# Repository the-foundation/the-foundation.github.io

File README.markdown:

Spacecraft
==========

This is [Spacecraft](http://spacecraft.org.nz)'s site.

Setup
-----

To check your system has the necessary dependencies, just run:

    script/setup

You can safely run this script as many times as you like.

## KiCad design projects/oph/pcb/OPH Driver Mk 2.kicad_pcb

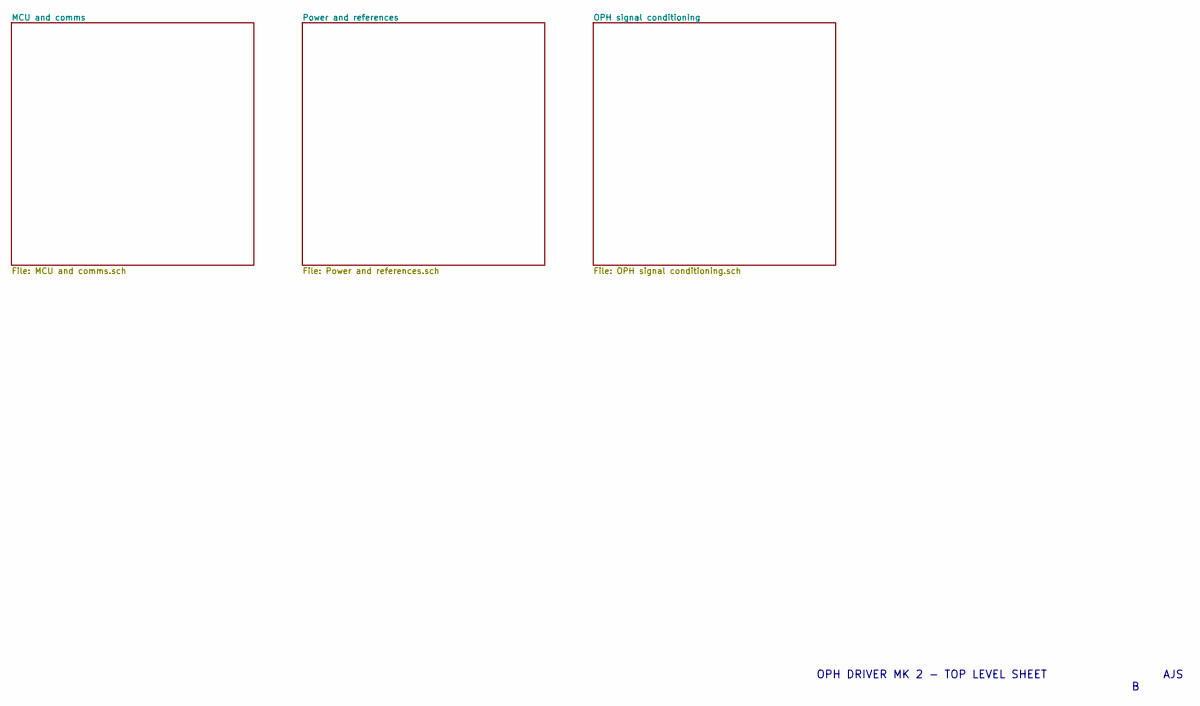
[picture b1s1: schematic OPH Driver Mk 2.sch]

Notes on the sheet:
OPH DRIVER MK 2 - TOP LEVEL SHEET
AJS

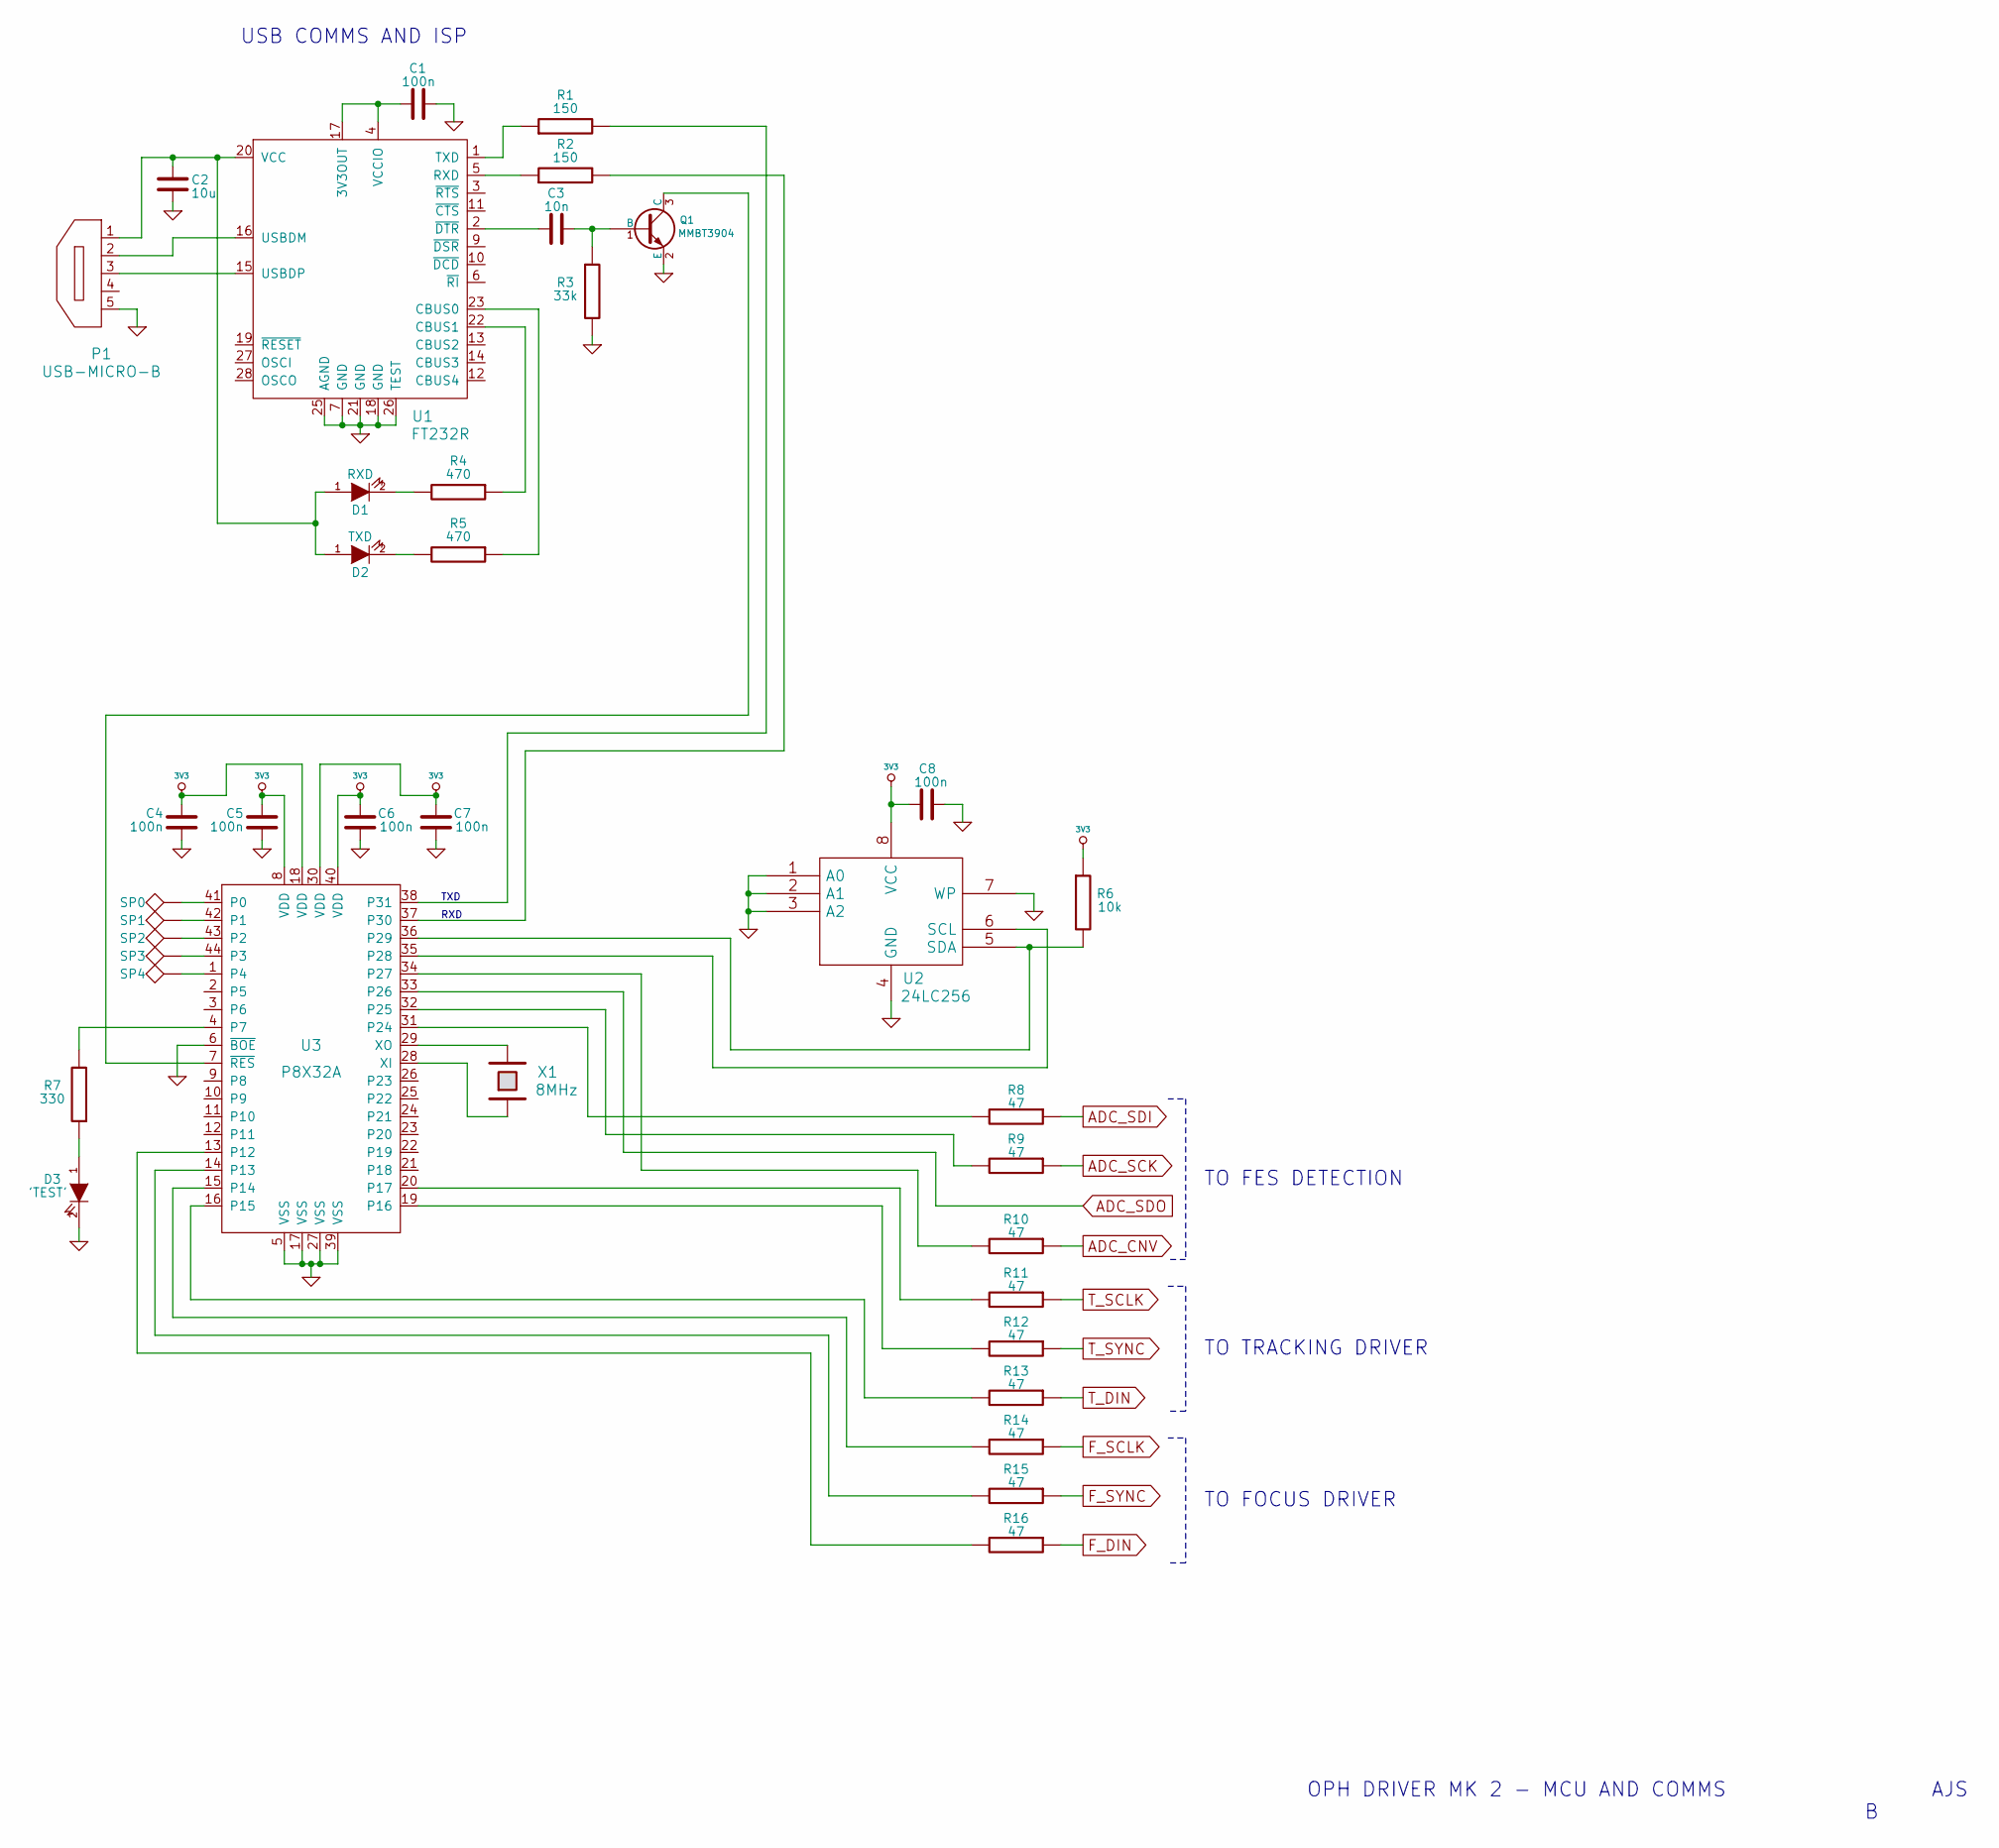
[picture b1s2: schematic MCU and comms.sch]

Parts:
C1, C4, C5, C6, C7, C8: 100n
C2: 10u
C3: 10n
D1: RXD
D2: TXD
D3: 'TEST'
P1: USB-MICRO-B
P2: SP0
P3: SP1
P4: SP2
P5: SP3
P6: SP4
Q1: MMBT3904; SOT-23
R1, R2: 150
R3: 33k
R4, R5: 470
R6: 10k
R7: 330
R8, R9, R10, R11, R12, R13, R14, R15, R16: 47
U1: FT232R
U2: 24LC256
U3: P8X32A
X1: 8MHz

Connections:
3V3: C4.1, C5.1, C6.1, C7.1, C8.2, R6.1, U2.8 (VCC), U3.8 (VDD), U3.18 (VDD), U3.30 (VDD), U3.40 (VDD); also elsewhere on the board
ADC_CNV: R10.1; also elsewhere on the board
ADC_SCK: R9.1; also elsewhere on the board
ADC_SDI: R8.1; also elsewhere on the board
ADC_SDO: U3.33 (P26); also elsewhere on the board
F_DIN: R16.1; also elsewhere on the board
F_SCLK: R14.1; also elsewhere on the board
F_SYNC: R15.1; also elsewhere on the board
GND: C1.2, C2.2, C4.2, C5.2, C6.2, C7.2, C8.1, D3.2 (K), P1.5, Q1.2 (E), R3.2, U1.7 (GND), U1.18 (GND), U1.21 (GND), U1.25 (AGND), U1.26 (TEST), U2.1 (A0), U2.2 (A1), U2.3 (A2), U2.4 (GND), U2.7 (WP), U3.5 (VSS), U3.6 (~BOE), U3.17 (VSS), U3.27 (VSS), U3.39 (VSS); also elsewhere on the board
unnamed: C1.1, U1.4 (VCCIO), U1.17 (3V3OUT)
unnamed: C2.1, D1.1 (A), D2.1 (A), P1.1, U1.20 (VCC)
unnamed: C3.1, U1.2 (~DTR)
unnamed: C3.2, Q1.1 (B), R3.1
unnamed: D1.2 (K), R4.2
unnamed: D2.2 (K), R5.2
unnamed: D3.1 (A), R7.1
unnamed: P1.2, U1.16 (USBDM)
unnamed: P1.3, U1.15 (USBDP)
unnamed: P2.1, U3.41 (P0)
unnamed: P3.1, U3.42 (P1)
unnamed: P4.1, U3.43 (P2)
unnamed: P5.1, U3.44 (P3)
unnamed: P6.1, U3.1 (P4)
unnamed: Q1.3 (C), U3.7 (~RES)
unnamed: R1.1, U1.1 (TXD)
unnamed: R1.2, U3.38 (P31)
unnamed: R2.1, U1.5 (RXD)
unnamed: R2.2, U3.37 (P30)
unnamed: R4.1, U1.22 (CBUS1)
unnamed: R5.1, U1.23 (CBUS0)
unnamed: R6.2, U2.5 (SDA), U3.36 (P29)
unnamed: R7.2, U3.4 (P7)
unnamed: R8.2, U3.31 (P24)
unnamed: R9.2, U3.32 (P25)
unnamed: R10.2, U3.34 (P27)
unnamed: R11.2, U3.20 (P17)
unnamed: R12.2, U3.19 (P16)
unnamed: R13.2, U3.16 (P15)
unnamed: R14.2, U3.15 (P14)
unnamed: R15.2, U3.14 (P13)
unnamed: R16.2, U3.13 (P12)
unnamed: U2.6 (SCL), U3.35 (P28)
unnamed: U3.28 (XI), X1.1
unnamed: U3.29 (XO), X1.2
T_DIN: R13.1; also elsewhere on the board
T_SCLK: R11.1; also elsewhere on the board
T_SYNC: R12.1; also elsewhere on the board

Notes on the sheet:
TXD
RXD
TO TRACKING DRIVER
USB COMMS AND ISP
OPH DRIVER MK 2 - MCU AND COMMS
TO FES DETECTION
TO FOCUS DRIVER
AJS

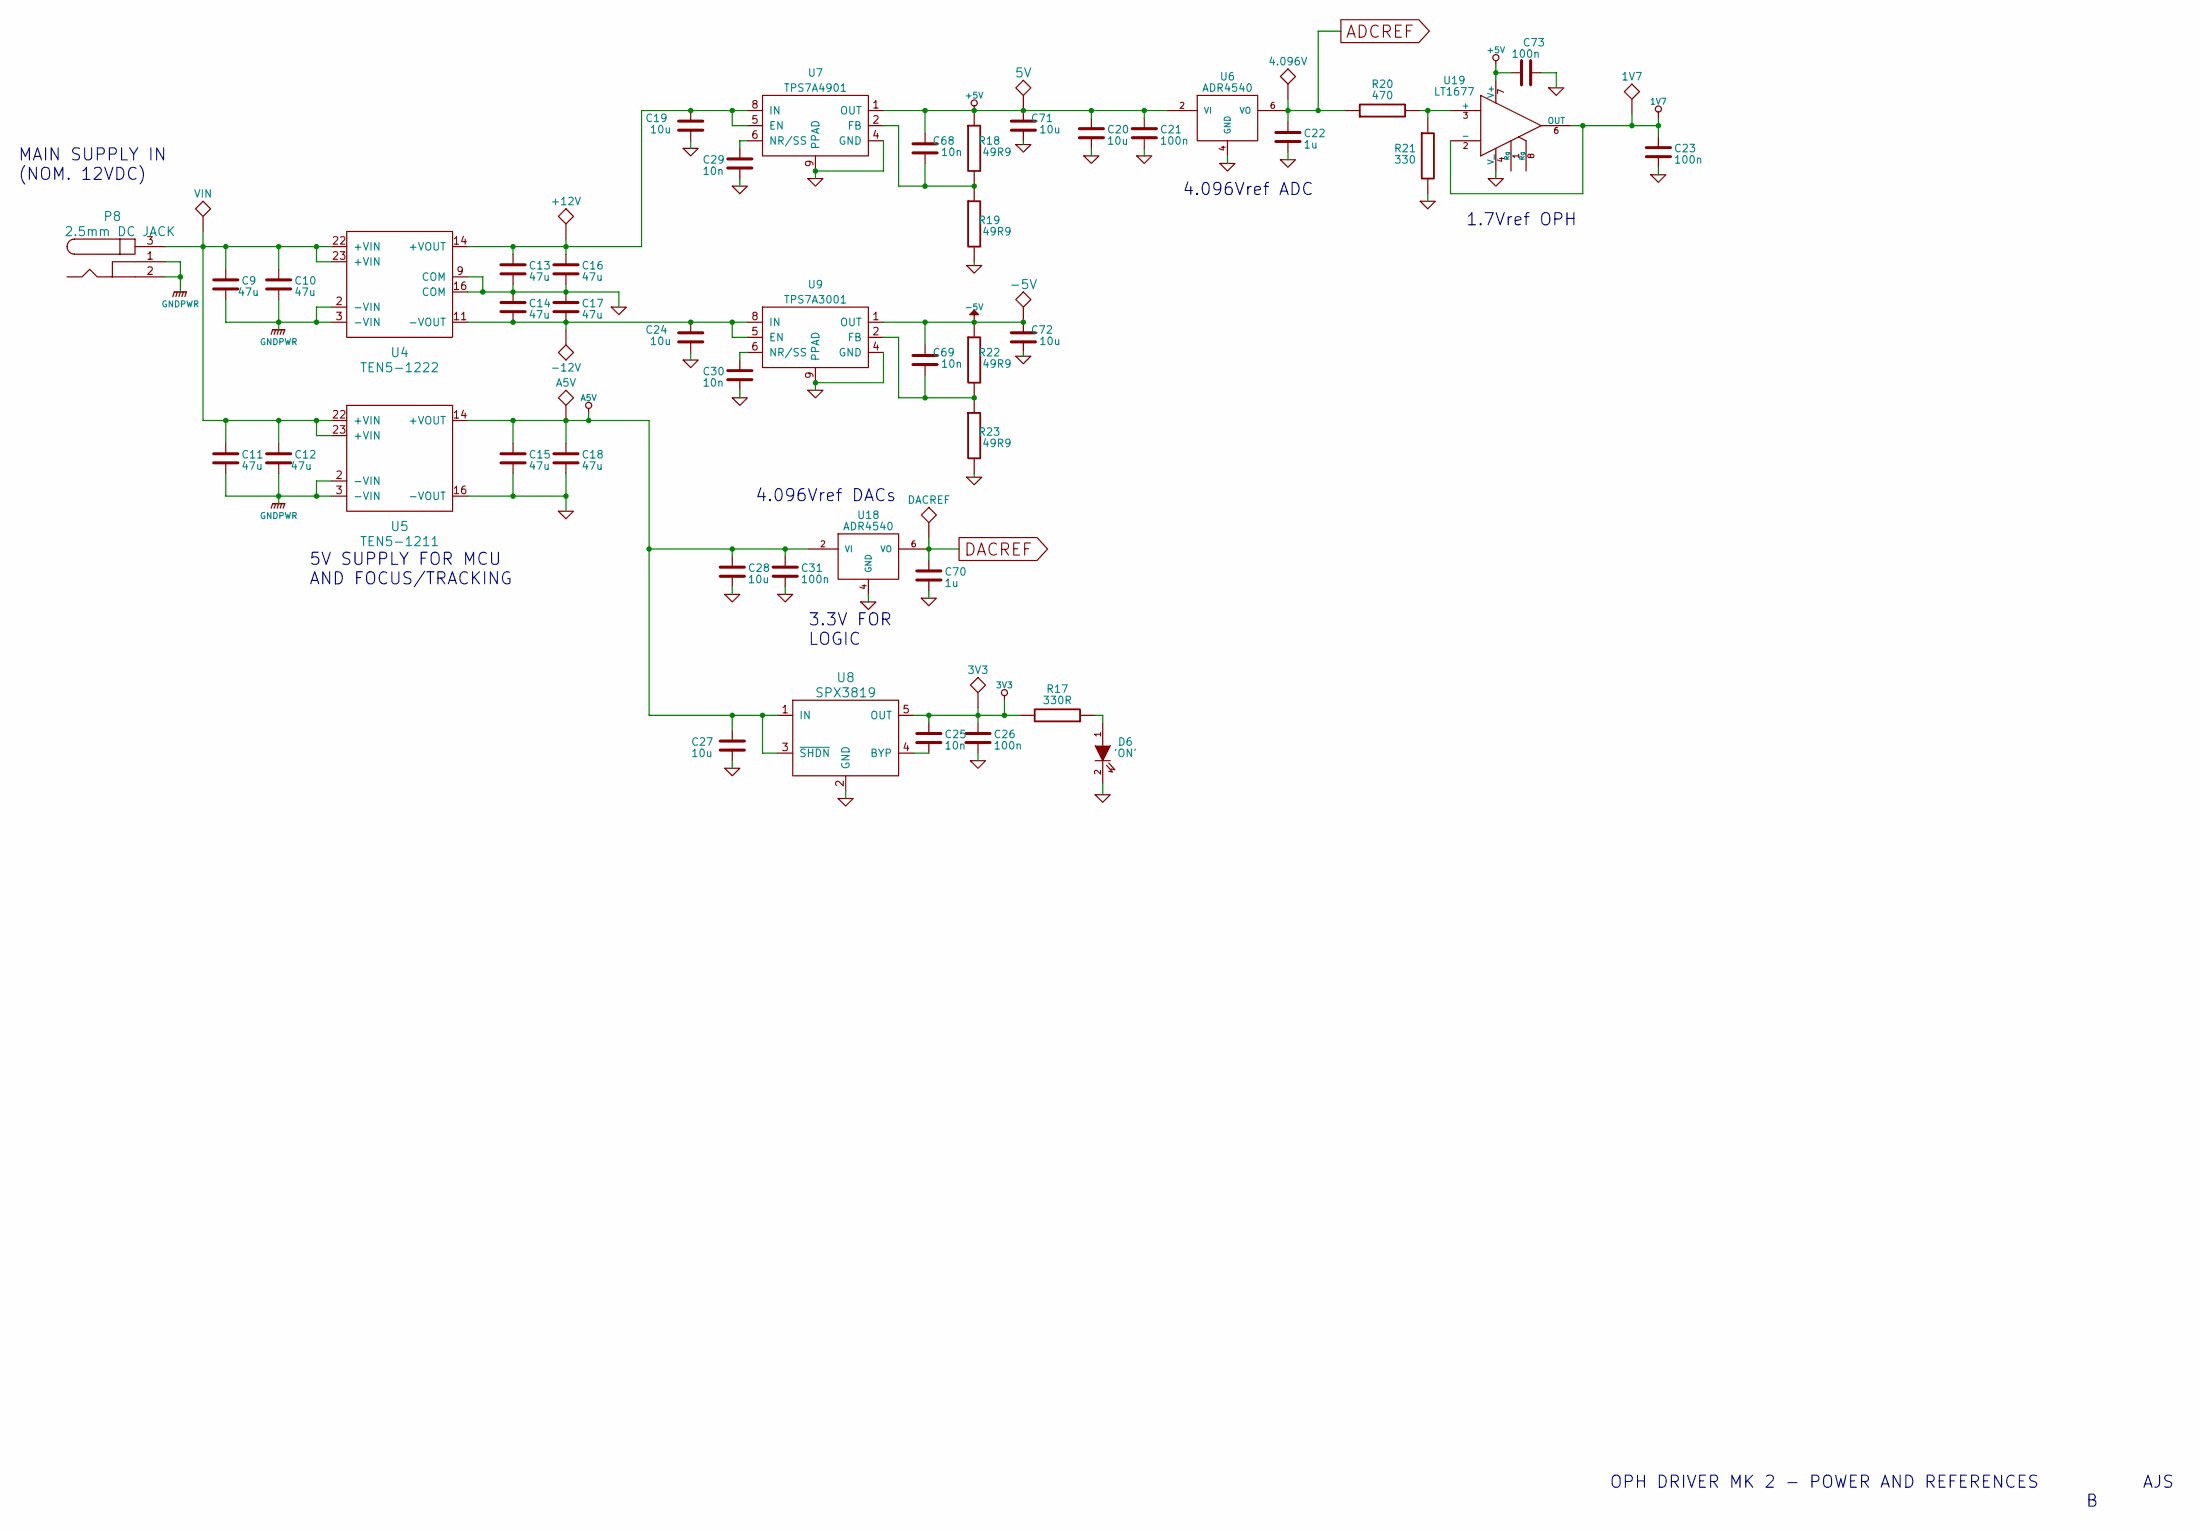
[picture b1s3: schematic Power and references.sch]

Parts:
C9, C10, C11, C12, C13, C14, C15, C16, C17, C18: 47u
C19, C20, C24, C27, C28, C71, C72: 10u
C21, C23, C26, C31, C73: 100n
C22, C70: 1u
C25, C29, C30, C68, C69: 10n
D6: 'ON'
P7: VIN
P8: 2.5mm DC JACK
P9: +12V
P10: 5V
P11: 4.096V
P12: 1V7
P13: A5V
P14: 3V3
P15: -12V
P51: DACREF
P52: -5V
R17: 330R
R18, R19, R22, R23: 49R9
R20: 470
R21: 330
U4: TEN5-1222
U5: TEN5-1211
U6, U18: ADR4540
U7: TPS7A4901
U8: SPX3819
U9: TPS7A3001
U19: LT1677

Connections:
1V7: C23.1, P12.1, U19.2 (-), U19.6 (OUT); also elsewhere on the board
3V3: C25.1, C26.1, P14.1, R17.2, U8.5 (OUT); also elsewhere on the board
-5V: C69.2, C72.2, P52.1, R22.1, U9.1 (OUT); also elsewhere on the board
A5V: C15.1, C18.1, C27.1, C28.1, C31.1, P13.1, U5.14 (+VOUT), U8.1 (IN), U8.3 (~SHDN), U18.2 (VI); also elsewhere on the board
ADCREF: C22.1, P11.1, R20.1, U6.6 (VO); also elsewhere on the board
DACREF: C70.1, P51.1, U18.6 (VO); also elsewhere on the board
GND: C13.2, C14.1, C15.2, C16.2, C17.1, C18.2, C19.1, C20.2, C21.2, C22.2, C23.2, C24.1, C26.2, C27.2, C28.2, C29.2, C30.2, C31.2, C70.2, C71.1, C72.1, C73.1, D6.2 (K), R19.2, R21.2, R23.2, U4.9 (COM), U4.16 (COM), U5.16 (-VOUT), U6.4 (GND), U7.4 (GND), U7.9 (PPAD), U8.2 (GND), U9.4 (GND), U9.9 (PPAD), U18.4 (GND), U19.4 (V_); also elsewhere on the board
GNDPWR: C9.2, C10.2, C11.2, C12.2, P8.1, P8.2, U4.2 (-VIN), U4.3 (-VIN), U5.2 (-VIN), U5.3 (-VIN)
unnamed: C9.1, C10.1, C11.1, C12.1, P7.1, P8.3, U4.22 (+VIN), U4.23 (+VIN), U5.22 (+VIN), U5.23 (+VIN)
unnamed: C13.1, C16.1, C19.2, P9.1, U4.14 (+VOUT), U7.5 (EN), U7.8 (IN)
unnamed: C14.2, C17.2, C24.2, P15.1, U4.11 (-VOUT), U9.5 (EN), U9.8 (IN)
unnamed: C25.2, U8.4 (BYP)
unnamed: C29.1, U7.6 (NR/SS)
unnamed: C30.1, U9.6 (NR/SS)
unnamed: C68.1, R18.2, R19.1, U7.2 (FB)
unnamed: C69.1, R22.2, R23.1, U9.2 (FB)
unnamed: D6.1 (A), R17.1
unnamed: R20.2, R21.1, U19.3 (+)

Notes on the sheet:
5V SUPPLY FOR MCU AND FOCUS/TRACKING
4.096Vref ADC
MAIN SUPPLY IN (NOM. 12VDC)
1.7Vref OPH
3.3V FOR LOGIC
OPH DRIVER MK 2 - POWER AND REFERENCES
AJS
4.096Vref DACs

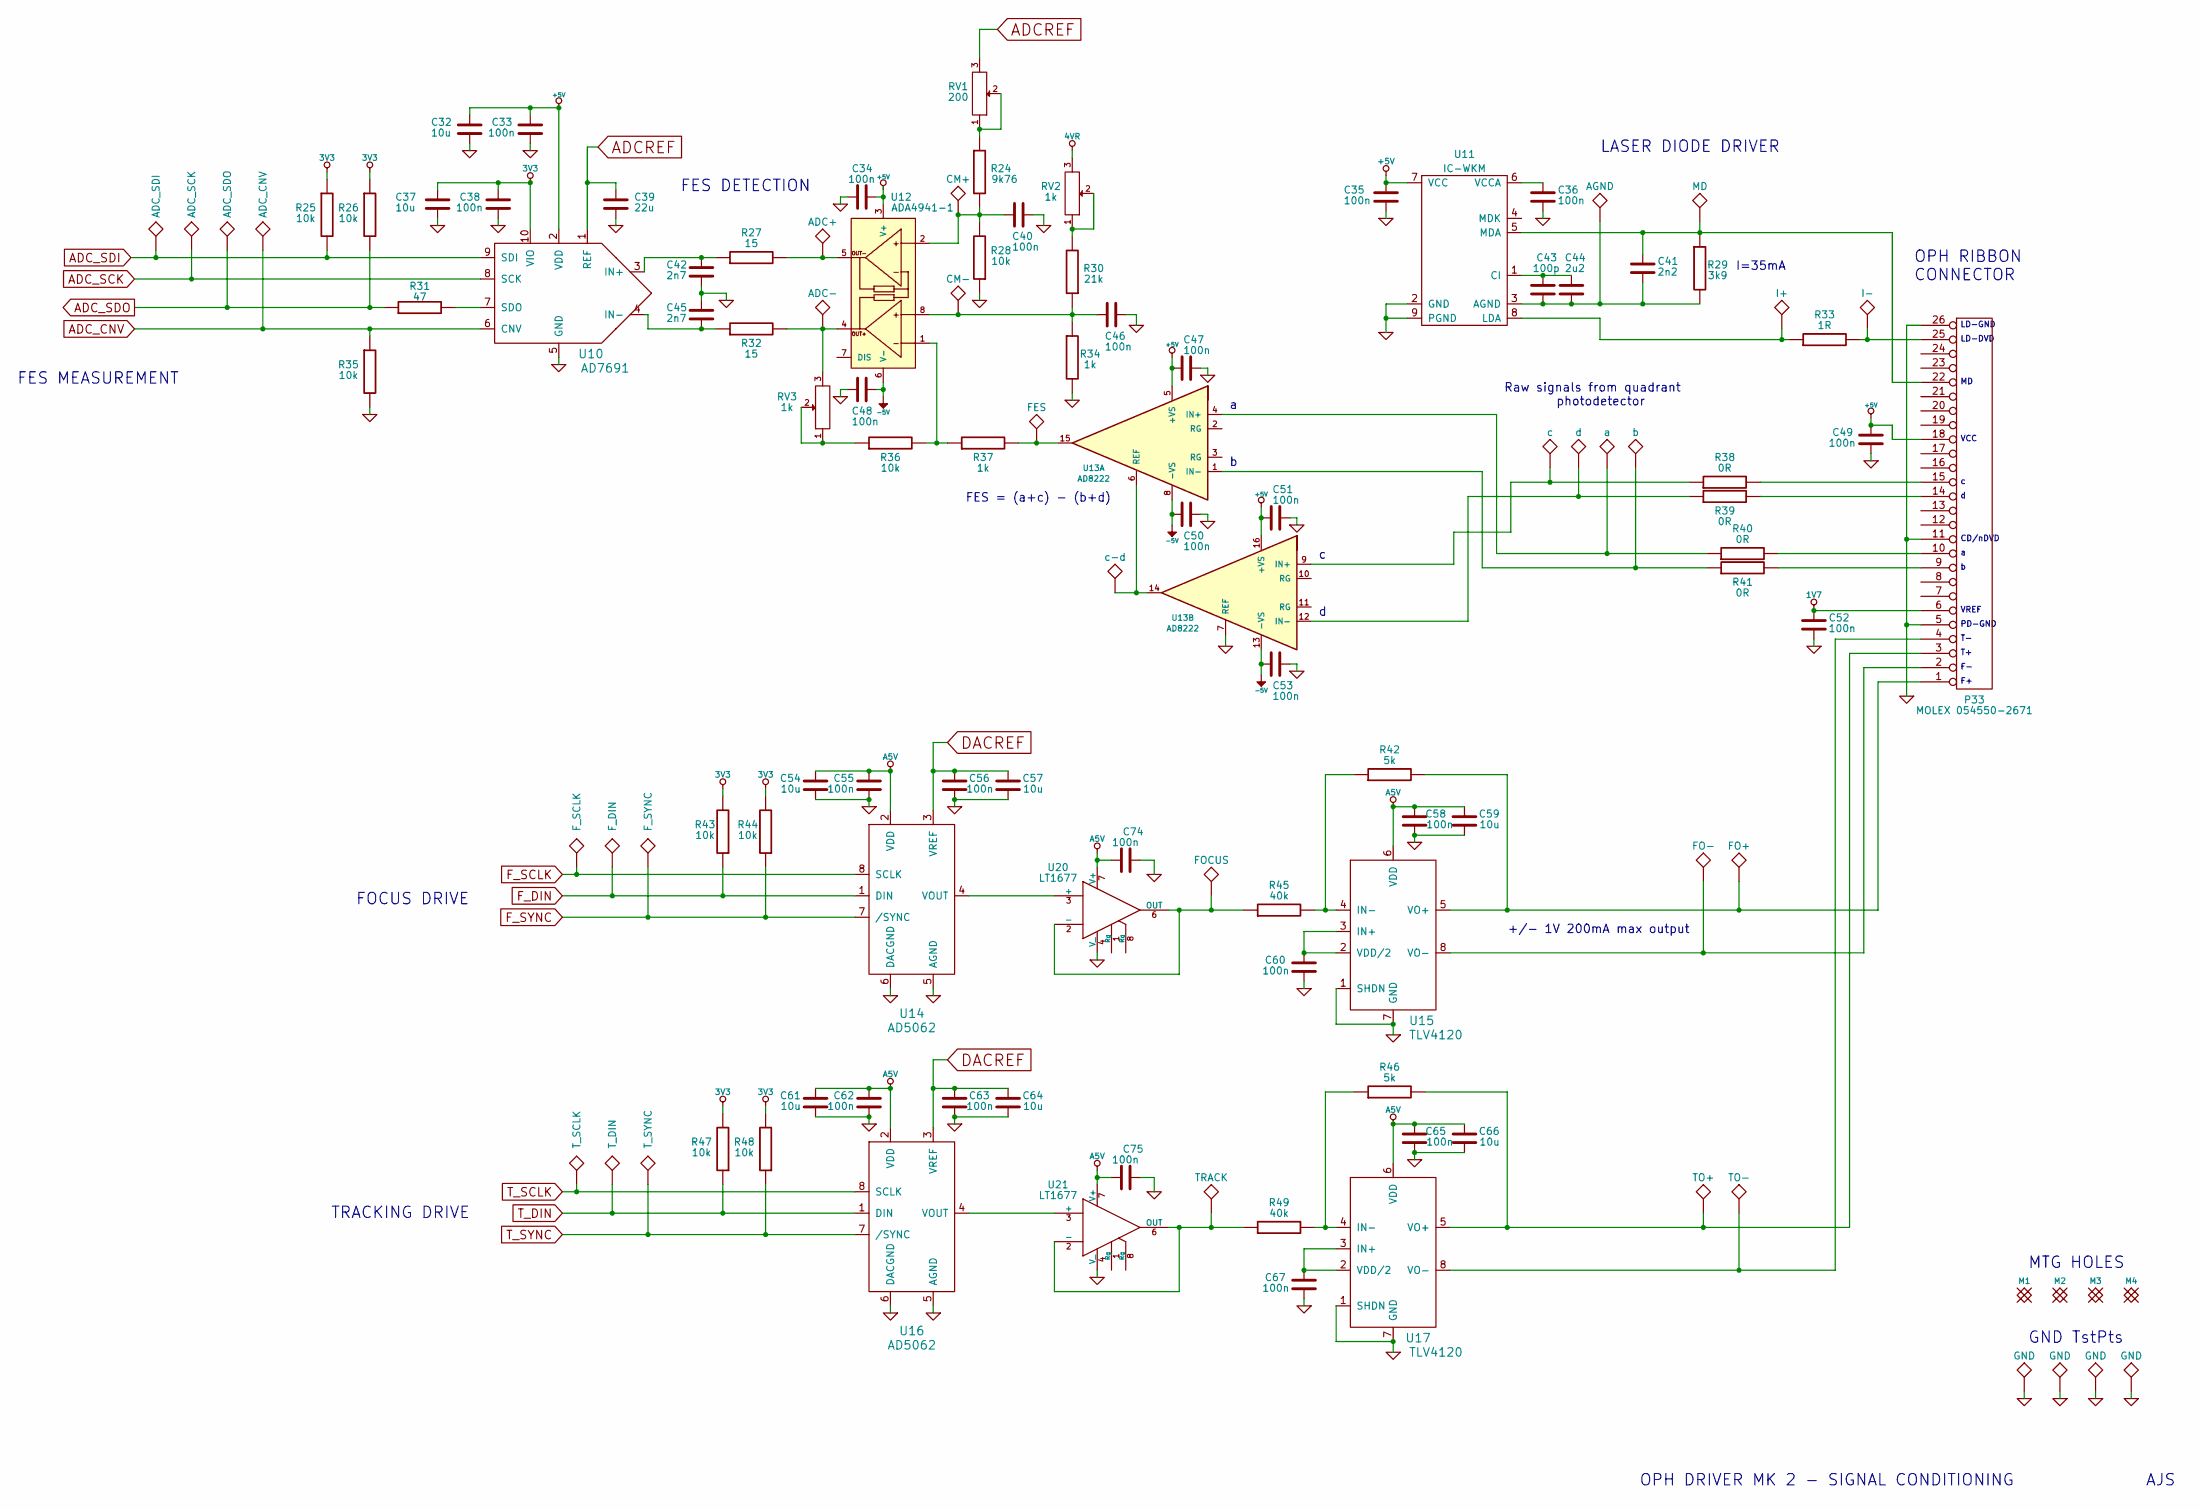
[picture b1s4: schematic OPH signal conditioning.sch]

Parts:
C32, C37, C54, C57, C59, C61, C64, C66: 10u
C33, C34, C35, C36, C38, C40, C46, C47, C48, C49, C50, C51, C52, C53, C55, C56, C58, C60, C62, C63, C65, C67, C74, C75: 100n
C39: 22u
C41: 2n2
C42, C45: 2n7
C43: 100p
C44: 2u2
M1, M2, M3, M4: MT-HOLE
P16: CM+
P17: AGND
P18: MD
P19: ADC_SDI
P20: ADC_SCK
P21: ADC_SDO
P22: ADC_CNV
P23: ADC+
P24: CM-
P25: ADC-
P26: I+
P27: I-
P28: FES
P29: c
P30: d
P31: a
P32: b
P33: MOLEX 054550-2671
P34: c-d
P35: F_SCLK
P36: F_DIN
P37: F_SYNC
P38: FO-
P39: FO+
P40: FOCUS
P41: T_SCLK
P42: T_DIN
P43: T_SYNC
P44: TRACK
P45: TO+
P46: TO-
P47, P48, P49, P50: GND
R24: 9k76
R25, R26, R28, R35, R36, R43, R44, R47, R48: 10k
R27, R32: 15
R29: 3k9
R30: 21k
R31: 47
R33: 1R
R34, R37: 1k
R38, R39, R40, R41: 0R
R42, R46: 5k
R45, R49: 40k
RV1: 200
RV2, RV3: 1k
U10: AD7691
U11: IC-WKM
U12: ADA4941-1
U13: AD8222
U14, U16: AD5062
U15, U17: TLV4120
U20, U21: LT1677

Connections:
1V7: C52.1, P33.6; also elsewhere on the board
3V3: C37.1, C38.1, R25.1, R26.1, R43.2, R44.2, R47.2, R48.2, U10.10 (VIO); also elsewhere on the board
4VR: RV2.3
-5V: C48.1, C50.2, C53.2, U12.6 (V-), U13.8 (-VS), U13.13 (-VS); also elsewhere on the board
A5V: C54.1, C55.1, C58.1, C59.1, C61.1, C62.1, C65.1, C66.1, C74.2, C75.2, U14.2 (VDD), U15.6 (VDD), U16.2 (VDD), U17.6 (VDD), U20.7 (V+), U21.7 (V+); also elsewhere on the board
ADCREF: C39.1, RV1.3, U10.1 (REF); also elsewhere on the board
ADC_CNV: P22.1, R35.1, U10.6 (CNV); also elsewhere on the board
ADC_SCK: P20.1, U10.8 (SCK); also elsewhere on the board
ADC_SDI: P19.1, R25.2, U10.9 (SDI); also elsewhere on the board
ADC_SDO: P21.1, R26.2, R31.1; also elsewhere on the board
DACREF: C56.1, C57.1, C63.1, C64.1, U14.3 (VREF), U16.3 (VREF); also elsewhere on the board
F_DIN: P36.1, R43.1, U14.1 (DIN); also elsewhere on the board
F_SCLK: P35.1, U14.8 (SCLK); also elsewhere on the board
F_SYNC: P37.1, R44.1, U14.7 (/SYNC); also elsewhere on the board
GND: C32.2, C33.2, C34.2, C35.2, C36.2, C37.2, C38.2, C39.2, C40.1, C42.2, C45.1, C46.1, C47.1, C48.2, C49.2, C50.1, C51.1, C52.2, C53.1, C54.2, C55.2, C56.2, C57.2, C58.2, C59.2, C60.2, C61.2, C62.2, C63.2, C64.2, C65.2, C66.2, C67.2, C74.1, C75.1, P33.5, P33.11, P33.26, P47.1, P48.1, P49.1, P50.1, R28.1, R34.2, R35.2, U10.5 (GND), U11.2 (GND), U11.9 (PGND), U13.7 (REF), U14.5 (AGND), U14.6 (DACGND), U15.1 (SHDN), U15.7 (GND), U16.5 (AGND), U16.6 (DACGND), U17.1 (SHDN), U17.7 (GND), U20.4 (V_), U21.4 (V_); also elsewhere on the board
unnamed: C36.1, U11.6 (VCCA)
unnamed: C40.2, P16.1, R24.2, R28.2, U12.2
unnamed: C41.1, P18.1, P33.22, R29.1, U11.5 (MDA)
unnamed: C41.2, C43.2, C44.2, P17.1, R29.2, U11.3 (AGND)
unnamed: C42.1, R27.1, U10.3 (IN+)
unnamed: C43.1, C44.1, U11.1 (CI)
unnamed: C45.2, R32.1, U10.4 (IN-)
unnamed: C46.2, P24.1, R30.1, R34.1, U12.8
unnamed: C60.1, U15.2 (VDD/2), U15.3 (IN+)
unnamed: C67.1, U17.2 (VDD/2), U17.3 (IN+)
unnamed: P23.1, R27.2, U12.5
unnamed: P25.1, R32.2, RV3.3, U12.4
unnamed: P26.1, R33.1, U11.8 (LDA)
unnamed: P27.1, P33.25, R33.2
unnamed: P28.1, R37.2, U13.15
unnamed: P29.1, R38.1, U13.9 (IN+)
unnamed: P30.1, R39.1, U13.12 (IN-)
unnamed: P31.1, R40.1, U13.4 (IN+)
unnamed: P32.1, R41.1, U13.1 (IN-)
unnamed: P33.1, P39.1, R42.2, U15.5 (VO+)
unnamed: P33.2, P38.1, U15.8 (VO-)
unnamed: P33.3, P45.1, R46.2, U17.5 (VO+)
unnamed: P33.4, P46.1, U17.8 (VO-)
unnamed: P33.9, R41.2
unnamed: P33.10, R40.2
unnamed: P33.14, R39.2
unnamed: P33.15, R38.2
unnamed: P34.1, U13.6 (REF), U13.14
unnamed: P40.1, R45.1, U20.2 (-), U20.6 (OUT)
unnamed: P44.1, R49.1, U21.2 (-), U21.6 (OUT)
unnamed: R24.1, RV1.1, RV1.2
unnamed: R30.2, RV2.1, RV2.2
unnamed: R31.2, U10.7 (SDO)
unnamed: R36.1, RV3.1, RV3.2
unnamed: R36.2, R37.1, U12.1
unnamed: R42.1, R45.2, U15.4 (IN-)
unnamed: R46.1, R49.2, U17.4 (IN-)
unnamed: U14.4 (VOUT), U20.3 (+)
unnamed: U16.4 (VOUT), U21.3 (+)
T_DIN: P42.1, R47.1, U16.1 (DIN); also elsewhere on the board
T_SCLK: P41.1, U16.8 (SCLK); also elsewhere on the board
T_SYNC: P43.1, R48.1, U16.7 (/SYNC); also elsewhere on the board

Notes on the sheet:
VCC
VREF
CD/nDVD
LD-DVD
LD-GND
PD-GND
LASER DIODE DRIVER
FES DETECTION
OPH RIBBON CONNECTOR
I=35mA
FES = (a+c) - (b+d)
FOCUS DRIVE
TRACKING DRIVE
+/- 1V 200mA max output
Raw signals from quadrant photodetector
OPH DRIVER MK 2 - SIGNAL CONDITIONING
FES MEASUREMENT
MTG HOLES
GND TstPts
AJS

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
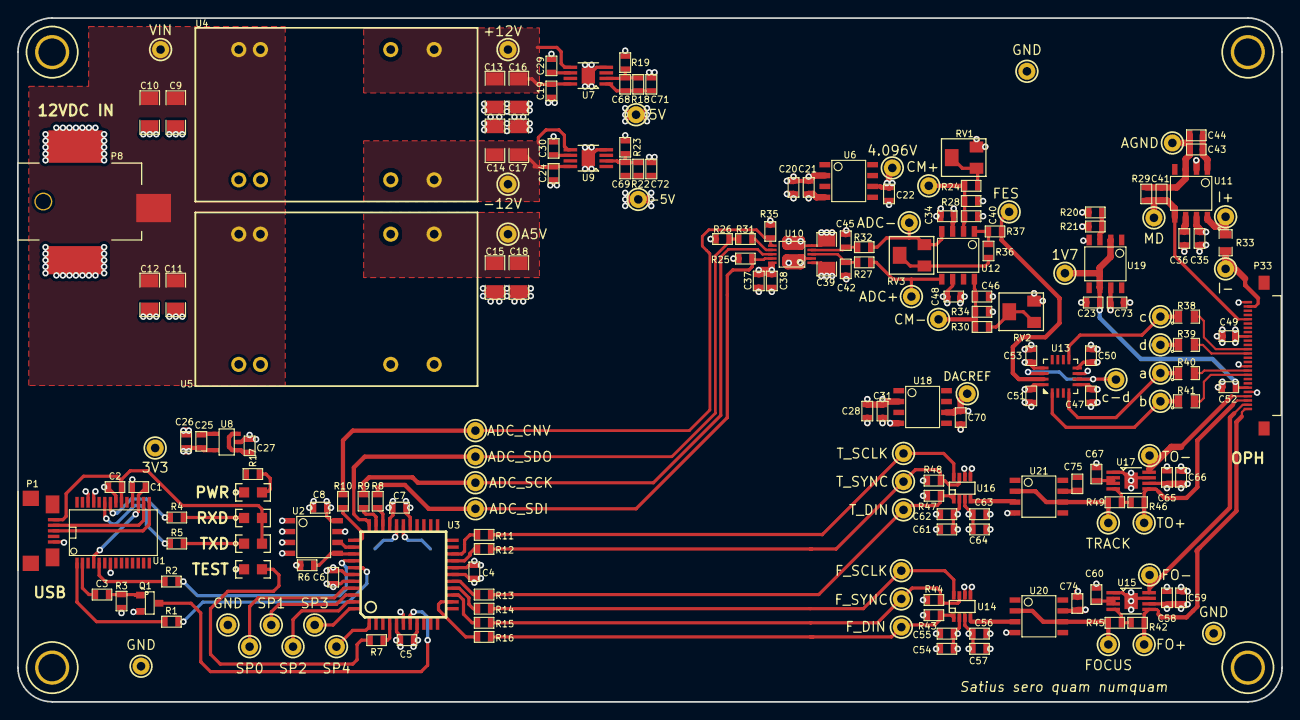
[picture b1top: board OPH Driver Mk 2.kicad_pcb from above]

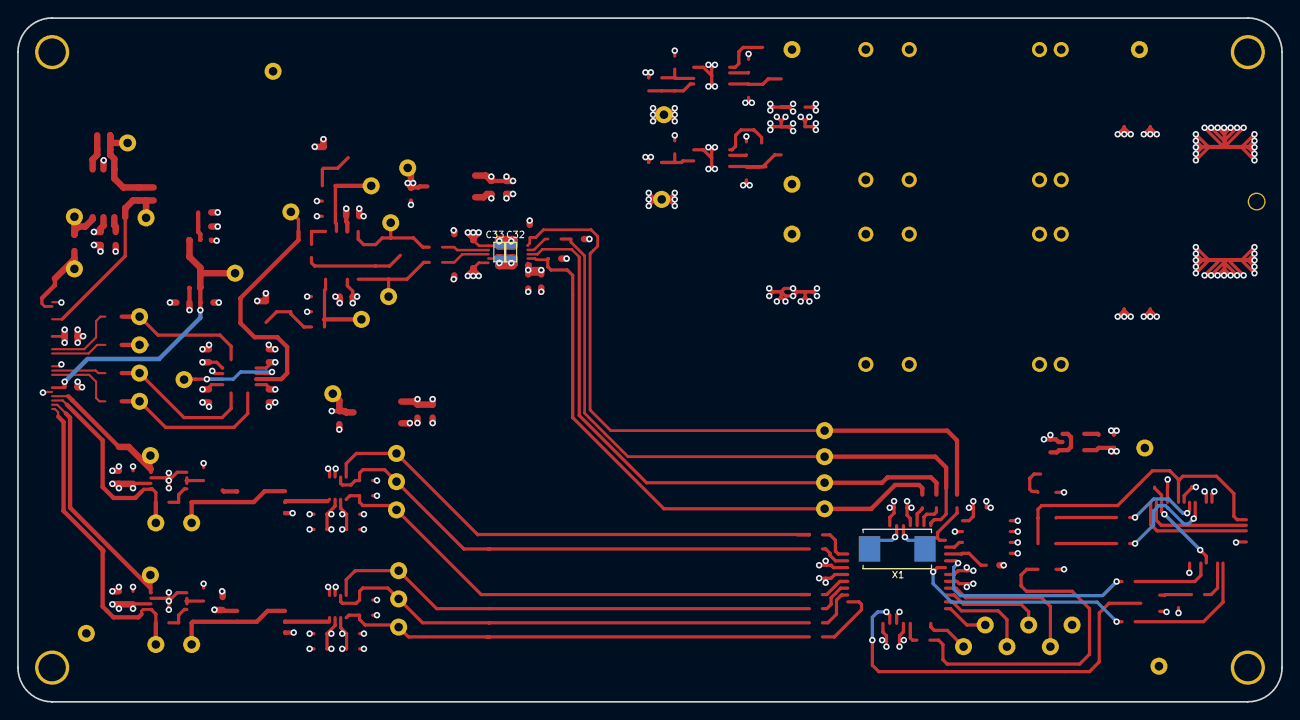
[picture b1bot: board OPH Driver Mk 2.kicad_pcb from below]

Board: 4 copper layers, 147.9 x 80.0 mm, 210 parts (3 on the bottom side), 104 nets.

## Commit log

2009-04-02 Added README.
2009-04-03 Added capfile.
2009-04-03 Added Phil's copy.
2009-04-03 Added a note about the casual Sunday session.
2009-04-05 Added Sinatra app.
2009-04-05 Added markup for header, navigation, and footer.
2009-04-05 Added some basic styles.
2009-04-05 Tweaked styles.
2009-04-05 Added logo.
2009-04-07 Updated note about Sundays.
2009-04-08 Ignoring .DS_Store.
2009-04-12 Moved HTML helpers to external lib.
2009-04-12 Updated layout.
2009-04-15 Tweaked layout.
2009-04-15 Tweaked logo.
2009-04-15 Added Google map.
2009-04-15 Updated map.
2009-04-15 Updated Capfile to restart thin.
2009-04-15 Added config rackup.
2009-04-18 Updated capfile to use domain name over IP.
2009-04-19 Updated event with time.
2009-04-20 Updated event for next Wed.
2009-04-27 Updated date.
2009-05-10 Added link to IRC.
2009-05-12 Updated To-Do list in README.
2009-05-13 Added Google Analytics.
2009-07-15 Updated IRC link.
2009-07-29 Updated README with "How to run locally" section.
    Updated "How to run locally" section in README.
2009-07-29 Added a section about getting the code.
    Added to the getting the code section.
2009-07-29 Switched port for shotgun.
2009-07-29 Removing next event line.
2009-07-29 Switching event background to green.
2009-07-29 Tweaked event style.
2009-07-29 Added a note about issues.
2009-07-29 Correcting spelling of "licence".
2009-09-02 Added database configuration and migration.
2009-09-02 Added rakefile, complete with database actions.
2009-09-02 Added Page model.
2009-09-02 Added routes for pages.
2009-09-02 Added fontend for pages.
2009-09-02 Added table styling.
2009-09-02 Added better listing and bulk deletion.
2009-09-02 Added root paths for pages.
2009-09-02 Added parent id migration.
2009-09-02 Added acts as tree to page model.
2009-09-02 Added acts as tree lib.
2009-09-02 Including acts as tree.
2009-09-02 Added form option for tree.
2009-09-02 Added breadcrumbs.
2009-09-02 Moved PeteWiki into its own module.
2009-09-02 Added parent field to page list table.
2009-09-02 Added authentication.
2009-09-02 Made a clearer capistrano deploy strategy.
2009-09-02 Added migration to deploy task.
2009-09-02 Tweaked database configuration.
2009-09-02 Wrapping migrate in a transaction.
2009-09-02 Fixed rake call.
2009-10-13 Verifying AR connections.
2009-10-13 Fixing AR verify! call.
2010-01-24 Renamed project to "Spacecraft".
2010-01-24 Updated logo to 'Spacecraft', added tagline.
2010-01-24 Added a note about start date.
2010-01-31 Added tagline to title tag.
2010-01-31 Added mailing list subscription form.
2010-02-01 Updated capfile to reflect new repository information.
2010-02-03 Updated Google Maps API key for Spacecraft.org.nz.
2010-02-04 Tweaked the README.
2010-03-24 Removed start date.
2010-06-16 Added logger 1.9 support.
2010-06-16 Updated event date.
2010-06-16 Ruby 1.9 compat.
2010-06-16 Made the Google Group more important.
2010-06-16 Removing Thin support in favour of Passenger.
2010-06-16 Better compatibility.
2011-04-13 Added hiatus message.
2013-02-12 Transition to Jekyll
2013-02-12 Add note about script/setup
2013-02-12 Add CNAME
2013-02-12 Remove ERB link
2013-06-08 Please stand by
2013-07-01 Update Gemfile source to use host rather than symbol
2013-07-01 Add link to mailling list
2013-07-01 Fix broken GitHub link
2013-08-18 Make it simpler to run a development server
2014-01-26 Introducing: The Foundation
2014-01-26 Add support for thefoundation.org.nz
2014-01-26 Improve mailing list form
2014-01-26 Add links to Google Group, Meetup, Twitter, GitHub
2014-01-26 Add build script
2014-02-10 Words
2014-02-10 Fix iOS button styling
2014-02-10 Render more readable on smartphones
2014-02-10 Centre headings in smartphone view
2014-02-10 Ignore vendor
    Hopefully fixes Travis build errors.
2014-02-15 Horizontally-align page when in mobile breakpoint
2014-03-13 Make the reasons fit onto one line (#hacky?)
2014-03-13 Add -moz equivalents for box-sizing
    Firefox doesn't support box-sizing yet.
2014-04-06 Tweak kit description
2014-04-07 Migrate to Kramdown
2014-09-09 Relocate script to bin
2014-09-13 Update GitHub Pages, restructure directories, adopt SCSS
2014-09-13 Set default layout to article
2014-09-13 Pretty permalinks (directory indexes)
2014-09-13 GitHub-themed syntax highlighting
2014-09-13 Default to the article layout
2014-09-13 Rename basic layout to bare
2014-09-13 Switch to white background
2014-09-13 Add Google Analytics tracking
2014-09-13 Dynamic page titles
2014-09-13 Relocate wrapping to body
2014-09-13 Refactor styles to use SCSS nesting
2014-09-13 Add main nav
2014-09-13 Move footer into bare layout, allow header to expand full-width
2014-09-13 Wrap page header
2014-09-13 Add Facebook link
2014-09-13 Pave the way for main navigation
2014-09-13 Strip out mobile styling
2014-09-13 Support custom page body class
2014-09-13 Fix YAML indentation
2014-09-13 Default to page layout
2014-09-13 Update github-pages
2014-09-14 Move site out of source directory
    GitHub Pages doesn't support a non-root source.
2014-09-14 Add authors data
2014-09-14 Basic blog
2014-09-14 Add Andrew to authors
2014-09-14 Add notes on writing blog posts
2014-09-14 Tweak heading
2014-09-14 Add build status badge [skip ci]
2014-09-14 Webkit font aliasing
2014-09-14 Use shiny new i3 for our 3D printer image :sparkles:
2014-09-14 Add about page
2014-09-14 Add map
2014-09-14 Change link order
2014-09-14 Projects
2014-09-14 Fix projects link
2014-09-15 Update bare.html
    Added link to blog
2014-09-15 Create 2014-09-14-Easy like Sunday Printing
2014-09-15 Added sunday session pics for 2014-09-14
2014-09-15 scaled down image size for blog post
2014-09-15 Scaled images down for blog post
2014-09-16 Added optical pickup head driver board to projects
2014-09-16 Update index.md
    Added oph description
2014-09-17 subfolder for images related to projects
2014-09-17 more oph project pics
2014-09-17 oph v2 updates
2014-09-22 images from sunday session 2014-09-22
2014-09-22 Create 2014-09-14-Printers printing printers
2014-09-22 Rename 2014-09-14-Printers printing printers to 2014-09-14-Printers printing printers.md
2014-09-23 Friendly URLs for blog posts
2014-09-28 Fix project markup
2014-09-28 Remove viewport
2014-10-15 added myself (Marek Kuziel) as blog author
2014-10-15 added blog post from sunday session from oct 12 2014
2014-10-15 resized photo for oct 12 blog entry to expected width (768px)
2014-10-15 fixed sep 21 blog entry date in the file name
2014-10-25 Improve syntax highlighting
2014-10-25 Add syntax highlighting to Oct 12 blog post
2014-10-27 fixed typo in 2014-10-12 blog post and added some more of fancy formatting
2014-10-28 added initial version of project
2014-11-05 added some more information about bittorrent and openweathermap to the sensor station project and updated the formatting of the project page
